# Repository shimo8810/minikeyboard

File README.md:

# minikeyboard

## 仕様

- 出力: CV/GATE 信号 (V/Hz)
- 音階: C4-B4 (多分)

## 回路図

## 配置

ユニバーサル基板用に配置

## 完成品

## 参照･参考

- https://info.shimamura.co.jp/digital/support/2020/02/136051
- https://www.arduino.cc/reference/en/libraries/mcp_dac/
- https://moutakusan.hatenablog.com/entry/2020/10/23/071000

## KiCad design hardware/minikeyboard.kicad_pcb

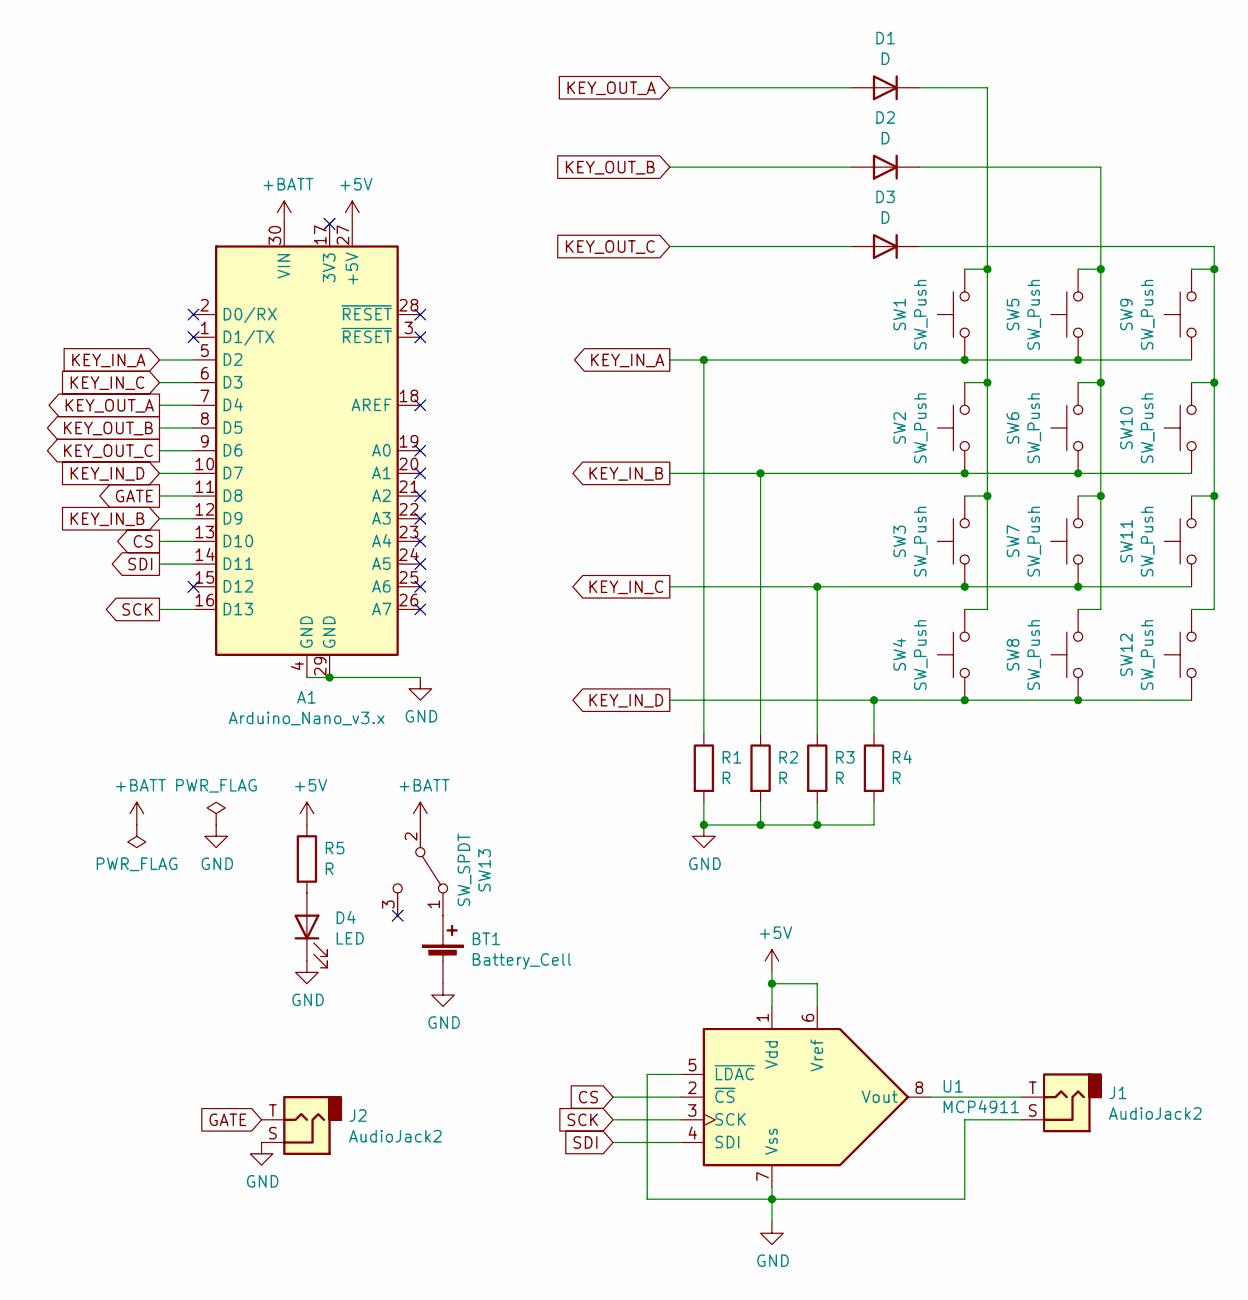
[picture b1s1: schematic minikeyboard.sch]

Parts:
A1: Arduino_Nano_v3.x; Arduino_Nano
BT1: Battery_Cell; SolderWire-0.1sqmm_1x02_P3.6mm_D0.4mm_OD1mm
D1, D2, D3: D; D_DO-35_SOD27_P7.62mm_Horizontal
D4: LED; LED_D5.0mm
J1, J2: AudioJack2; Jack_6.35mm_Neutrik_NJ2FD-V_Vertical
R1, R2, R3, R4, R5: R; R_Axial_DIN0207_L6.3mm_D2.5mm_P7.62mm_Horizontal
SW1, SW2, SW3, SW4, SW5, SW6, SW7, SW8, SW9, SW10, SW11, SW12: SW_Push; SW_Tactile_Straight_KSA0Axx1LFTR
SW13: SW_SPDT; SW_Slide_1P2T_CK_OS102011MS2Q
U1: MCP4911; DIP-8_W7.62mm_Socket

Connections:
+5V: A1.27 (+5V), R5.1, U1.1 (Vdd), U1.6 (Vref)
+BATT: A1.30 (VIN), SW13.2 (B)
CS: A1.13 (D10), U1.2 (~CS)
GATE: A1.11 (D8), J2.T
GND: A1.4 (GND), A1.29 (GND), BT1.2 (-), D4.1 (K), J1.S, J2.S, R1.2, R2.2, R3.2, R4.2, U1.5 (~LDAC), U1.7 (Vss)
KEY_IN_A: A1.5 (D2), R1.1, SW1.1, SW5.1, SW9.1
KEY_IN_B: A1.12 (D9), R2.1, SW2.1, SW6.1, SW10.1
KEY_IN_C: A1.6 (D3), R3.1, SW3.1, SW7.1, SW11.1
KEY_IN_D: A1.10 (D7), R4.1, SW4.1, SW8.1, SW12.1
KEY_OUT_A: A1.7 (D4), D1.2 (A)
KEY_OUT_B: A1.8 (D5), D2.2 (A)
KEY_OUT_C: A1.9 (D6), D3.2 (A)
unnamed: BT1.1 (+), SW13.1 (A)
unnamed: D1.1 (K), SW1.2, SW2.2, SW3.2, SW4.2
unnamed: D2.1 (K), SW5.2, SW6.2, SW7.2, SW8.2
unnamed: D3.1 (K), SW9.2, SW10.2, SW11.2, SW12.2
unnamed: D4.2 (A), R5.2
unnamed: J1.T, U1.8 (Vout)
SCK: A1.16 (D13), U1.3 (SCK)
SDI: A1.14 (D11), U1.4 (SDI)

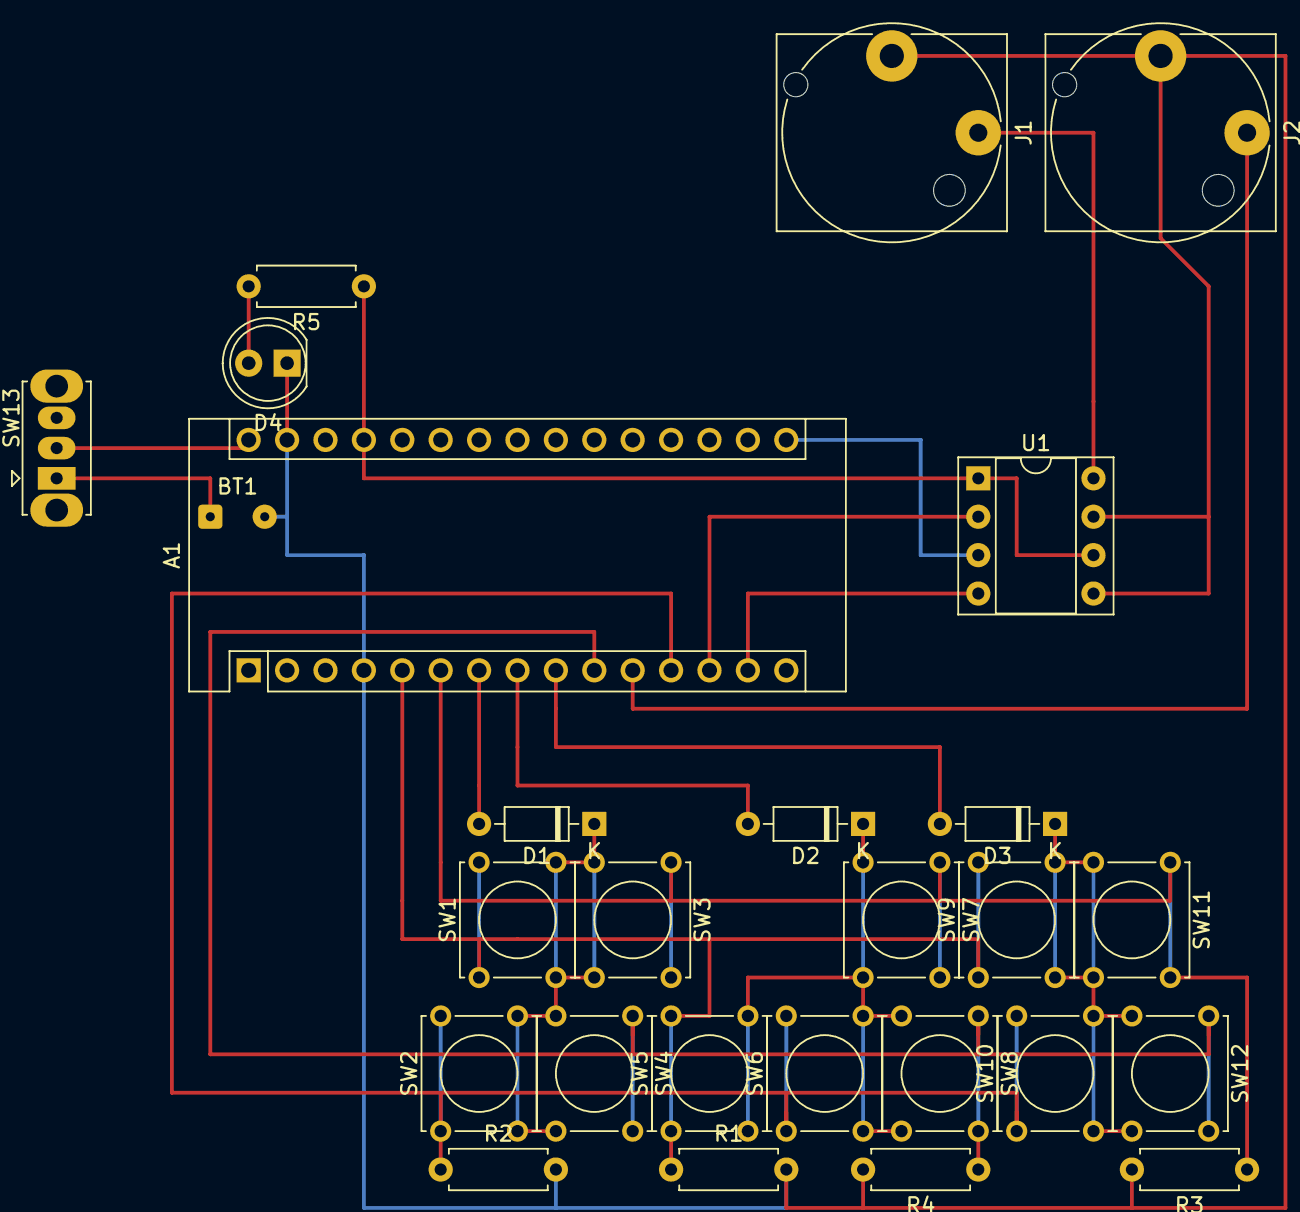
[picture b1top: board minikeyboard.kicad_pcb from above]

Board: 2 copper layers, 27 parts (0 on the bottom side), 20 nets.

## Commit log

2021-09-09 [add] init commit
2021-09-09 [update] change directory
2021-09-09 [add] add hardware data
2021-09-09 [update] ignore kicad file
2021-09-09 [add] add images
2021-09-09 [update] add sample images
2021-09-09 [update] add ref
2021-09-09 Create LICENSE
